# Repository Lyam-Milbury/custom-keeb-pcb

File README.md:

# 8/1 Macropad PCB
Repo for my (mis)adventures in creating a custom PCB for a macropad. I have always been a fan of custom keyboards. My daily driver is a stripped-down DROP ALT keyboard. I replaced the switches with ones that I hand-lubed, swapped the stabilizers with higher quality ones, and fitted custom keycaps to complete the build. After falling even further down the rabbit hole, the only natural progression of this hobby was clearly to create a custom PCB. This PCB has 8 slots for MX-hybrid switches (no LED pins) and 1 rotary encoder (hence, 8/1). The design of this build was inspired by ai03's <a href="https://wiki.ai03.com/books/pcb-design/chapter/pcb-designer-guide">PCB Designer Guide</a>.

## Software
KiCad 7.0 was used to create the schematics and design for the PCB. A custom footprint library, MX_ALPS_HYBRID, was used for the switch slot footprints, but everything else is available on vanilla KiCad.

## Schematics
The following are images of the schematics that were created in KiCad. This schematics file was then used to generate the PCB template.
### Microcontroller Unit

The Microcontroller unit (MCU) used for this project was the ATMega32U4-A. This microcontroller is perfect for this application, as this project did not require a large amount of processing power. It boasts a humble 44 pins, 24 of which can be used as bi-directional I/O ports for the signals sent by our key presses. This design could easily be scaled up to a fully sized keyboard matrix and this MCU would still have pins to spare. It also has 32 KBs of flash memory with is more than enough for the firmware that will be flashed onto it.

### Auxillary Units 

The rest of the schematics include the following:
* 3x4 keyboard matrix created using diodes as switches
* Decoupling capacitors to filter out electrical noise
* A crystal which controls the speed of the MCU
* A reset button for testing purposes
* The USB 2.0 circutry
  
|Keyboard Matrix|Decoupling Capacitor, Crystal, Reset Button, USB connection|
-----------------------|-------------------------------------------------------------
 | 

## PCB Designs

### Version 1 

This was the first design I came up with. As soon as I finished it, I already knew I wasn't too proud of it. The traces were messy and the placement of some of the components wasn't optimal.

### Version 2

Version two is the latest design. I moved the MCU and the reset switch to allow connections to be traced with more ease. IMore care in laying out the traces, opting for bus-style traces wherever I could. while keeping in mind that some traces needed to be intentionally isolated to prevent crosstalk. I knew this design would be good enough for production, so I also added final touches, such as the drill holes in the bottom corners, the ground fill in the top third to protect sensitive components from electrical noise, and a print of a little dude pressing the reset button.

## TODOs & Note
The design has already been sent to a manufacturer and is in production as I'm typing this. Once I receive the boards, if everything works as expected, here are the next steps I'll be taking to complete this project:
1. Solder components to the PCB
2. Use QMK to write custom macros
3. Design & 3d print enclosure

Designing this PCB has been a blast. I'm a computer engineer by education but I took more of a software-oriented route for my trade. This has reminded me of how much fun hardware design can be and will not be the last one design.

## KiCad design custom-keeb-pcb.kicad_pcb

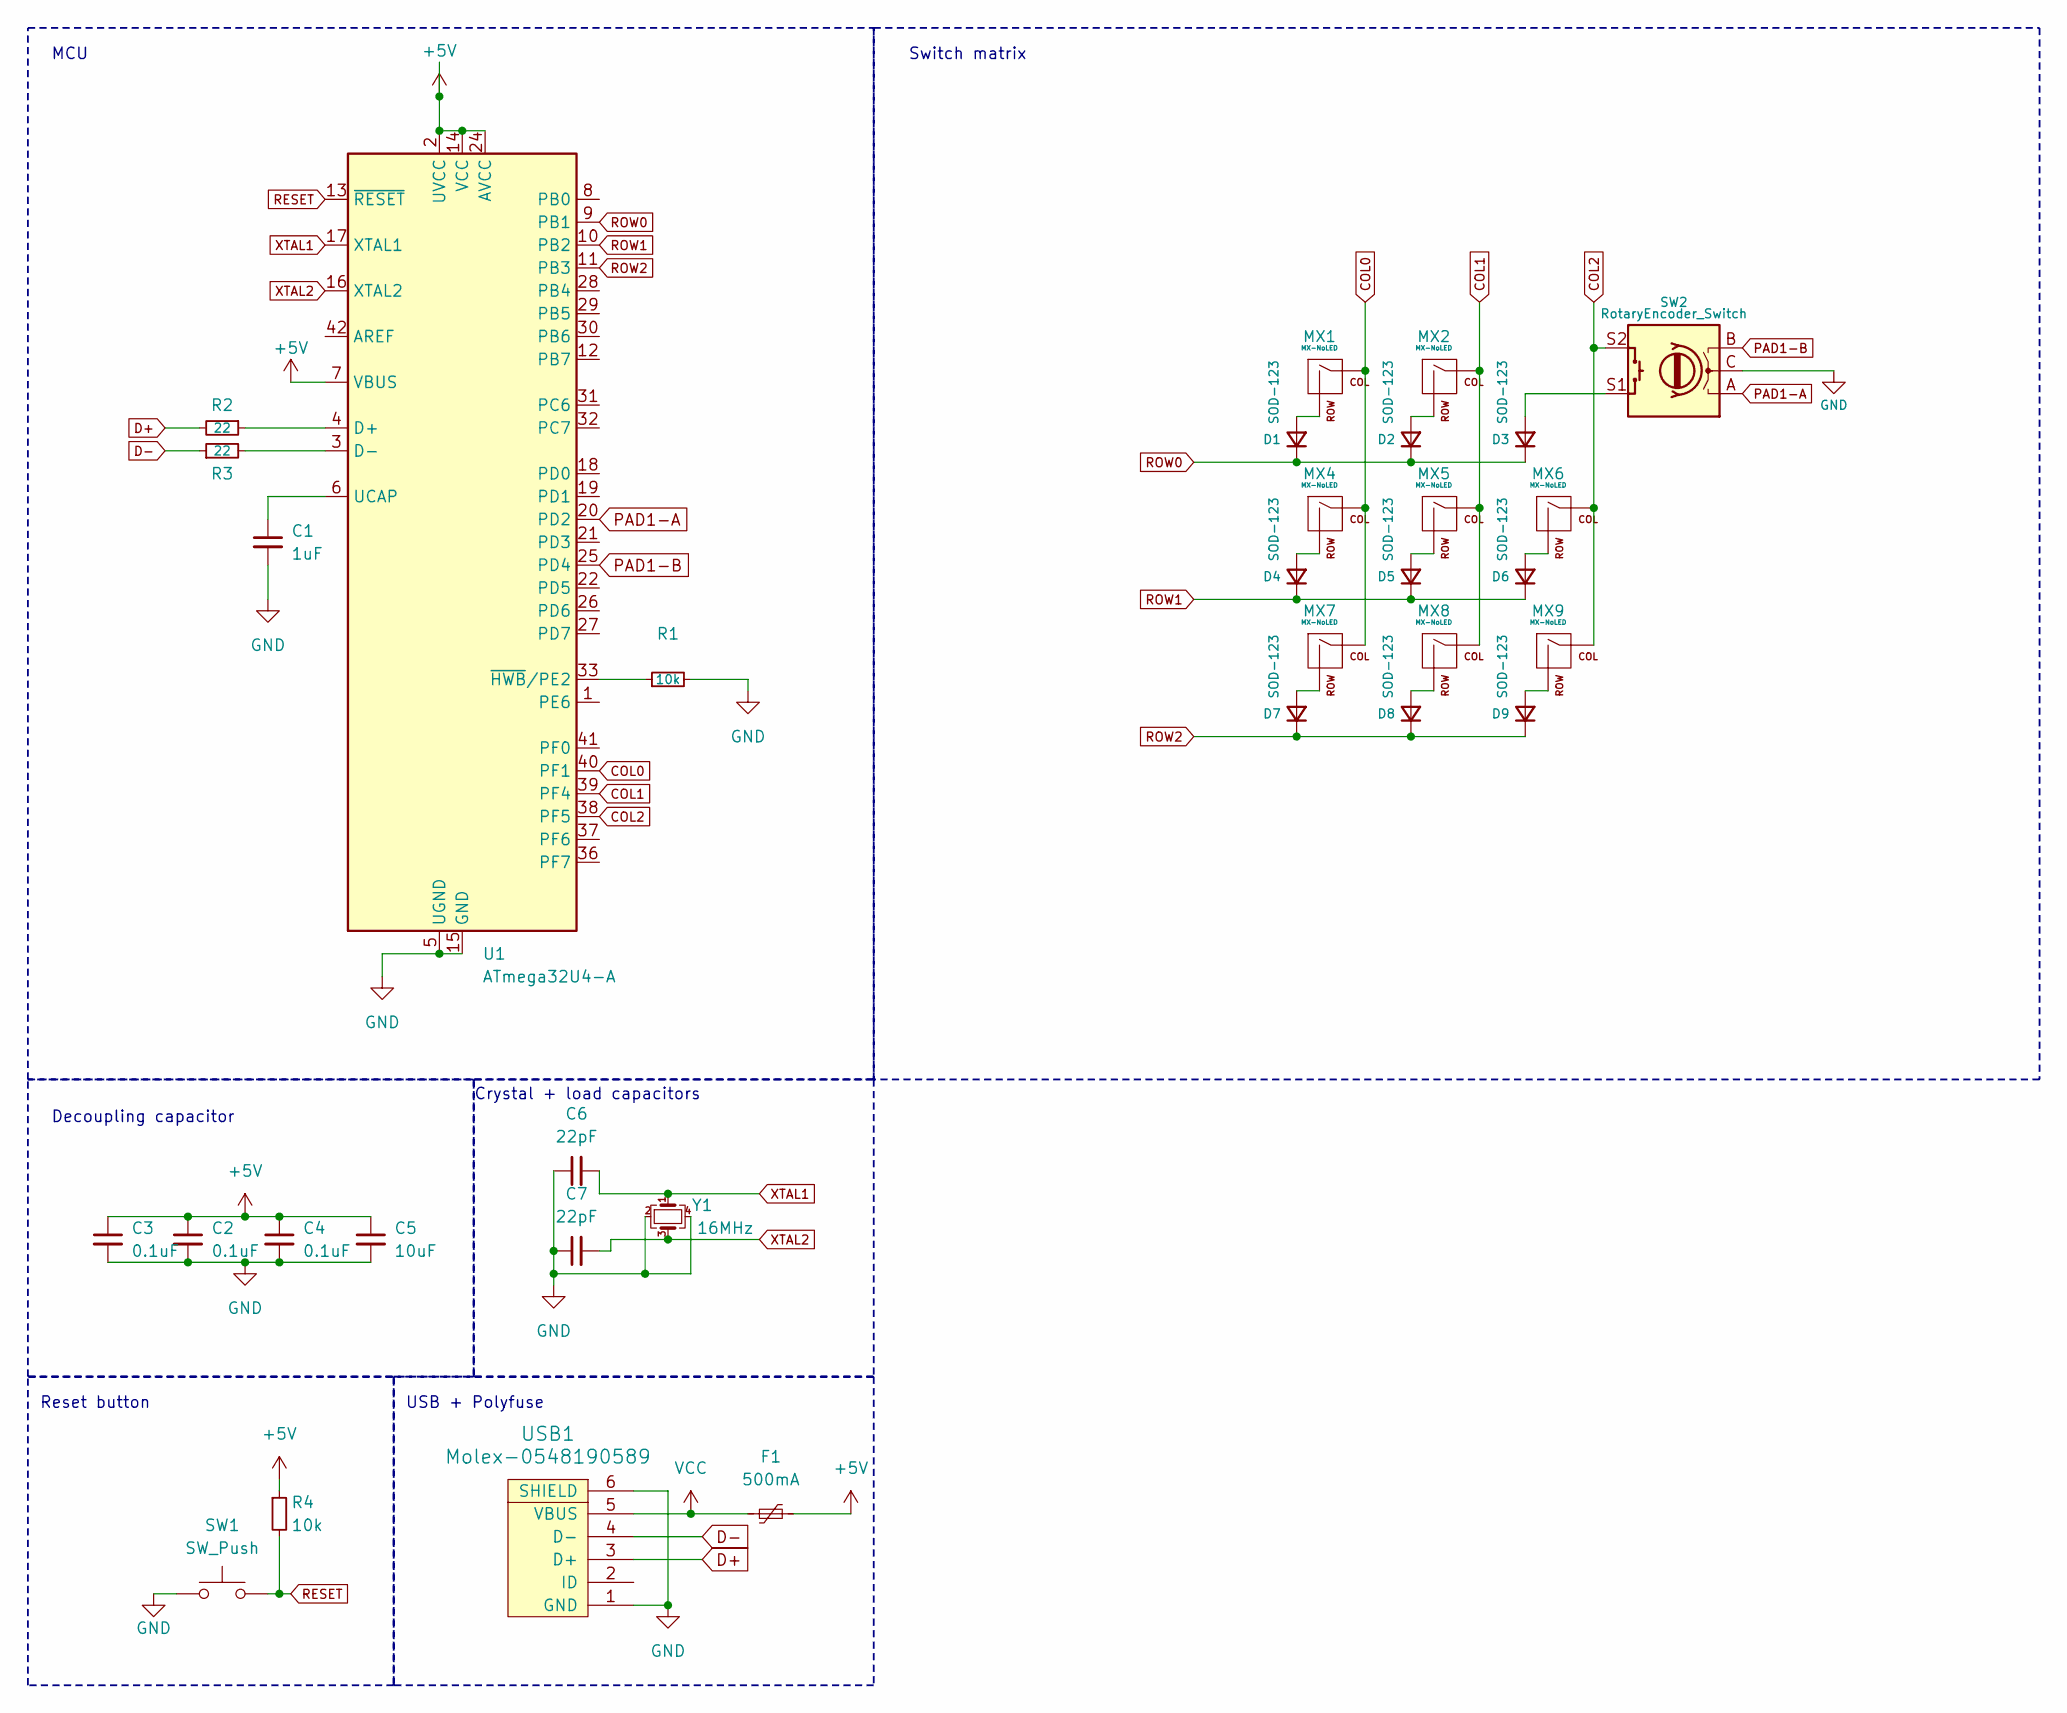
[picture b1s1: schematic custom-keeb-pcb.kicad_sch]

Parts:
C1: 1uF; C_0805_2012Metric
C2, C3, C4: 0.1uF; C_0805_2012Metric
C5: 10uF; C_0805_2012Metric
C6, C7: 22pF; C_0805_2012Metric
D1, D2, D3, D4, D5, D6, D7, D8, D9: SOD-123; D_SOD-123
F1: 500mA; Fuse_1206_3216Metric
MX1, MX2, MX4, MX5, MX6, MX7, MX8, MX9: MX-NoLED; MX-1U-NoLED
R1, R4: 10k; R_0805_2012Metric
R2, R3: 22; R_0805_2012Metric
SW1: SW_Push; SKQG-1155865
SW2: RotaryEncoder_Switch; RotaryEncoder_Alps_EC11E-Switch_Vertical_H20mm
U1: ATmega32U4-A; TQFP-44_10x10mm_P0.8mm
USB1: Molex-0548190589
Y1: 16MHz; Crystal_SMD_3225-4Pin_3.2x2.5mm

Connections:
+5V: C2.1, C3.1, C4.1, C5.1, F1.2, R4.1, U1.2 (UVCC), U1.7 (VBUS), U1.14 (VCC), U1.24 (AVCC), U1.34 (VCC), U1.44 (AVCC)
COL0: MX1.1 (COL), MX4.1 (COL), MX7.1 (COL), U1.40 (PF1)
COL1: MX2.1 (COL), MX5.1 (COL), MX8.1 (COL), U1.39 (PF4)
COL2: MX6.1 (COL), MX9.1 (COL), SW2.S2, U1.38 (PF5)
D+: R2.2, USB1.3 (D+)
D-: R3.1, USB1.4 (D-)
GND: C1.2, C2.2, C3.2, C4.2, C5.2, C6.1, C7.1, R1.2, SW1.1, SW2.C, U1.5 (UGND), U1.15 (GND), U1.23 (GND), U1.35 (GND), U1.43 (GND), USB1.1 (GND), USB1.6 (SHIELD), Y1.2, Y1.4
unnamed: D1.2 (A), MX1.2 (ROW)
unnamed: D2.2 (A), MX2.2 (ROW)
unnamed: D3.2 (A), SW2.S1
unnamed: D4.2 (A), MX4.2 (ROW)
unnamed: D5.2 (A), MX5.2 (ROW)
unnamed: D6.2 (A), MX6.2 (ROW)
unnamed: D7.2 (A), MX7.2 (ROW)
unnamed: D8.2 (A), MX8.2 (ROW)
unnamed: D9.2 (A), MX9.2 (ROW)
unnamed: R2.1, U1.4 (D+)
unnamed: R3.2, U1.3 (D-)
unnamed: C1.1, U1.6 (UCAP)
unnamed: R1.1, U1.33 (~HWB/PE2)
PAD1-A: SW2.A, U1.20 (PD2)
PAD1-B: SW2.B, U1.25 (PD4)
RESET: R4.2, SW1.2, U1.13 (~RESET)
ROW0: D1.1 (K), D2.1 (K), D3.1 (K), U1.9 (PB1)
ROW1: D4.1 (K), D5.1 (K), D6.1 (K), U1.10 (PB2)
ROW2: D7.1 (K), D8.1 (K), D9.1 (K), U1.11 (PB3)
VCC: F1.1, USB1.5 (VBUS)
XTAL1: C6.2, U1.17 (XTAL1), Y1.1
XTAL2: C7.2, U1.16 (XTAL2), Y1.3

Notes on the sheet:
Switch matrix
Reset button
Crystal + load capacitors
MCU
USB + Polyfuse
Decoupling capacitor

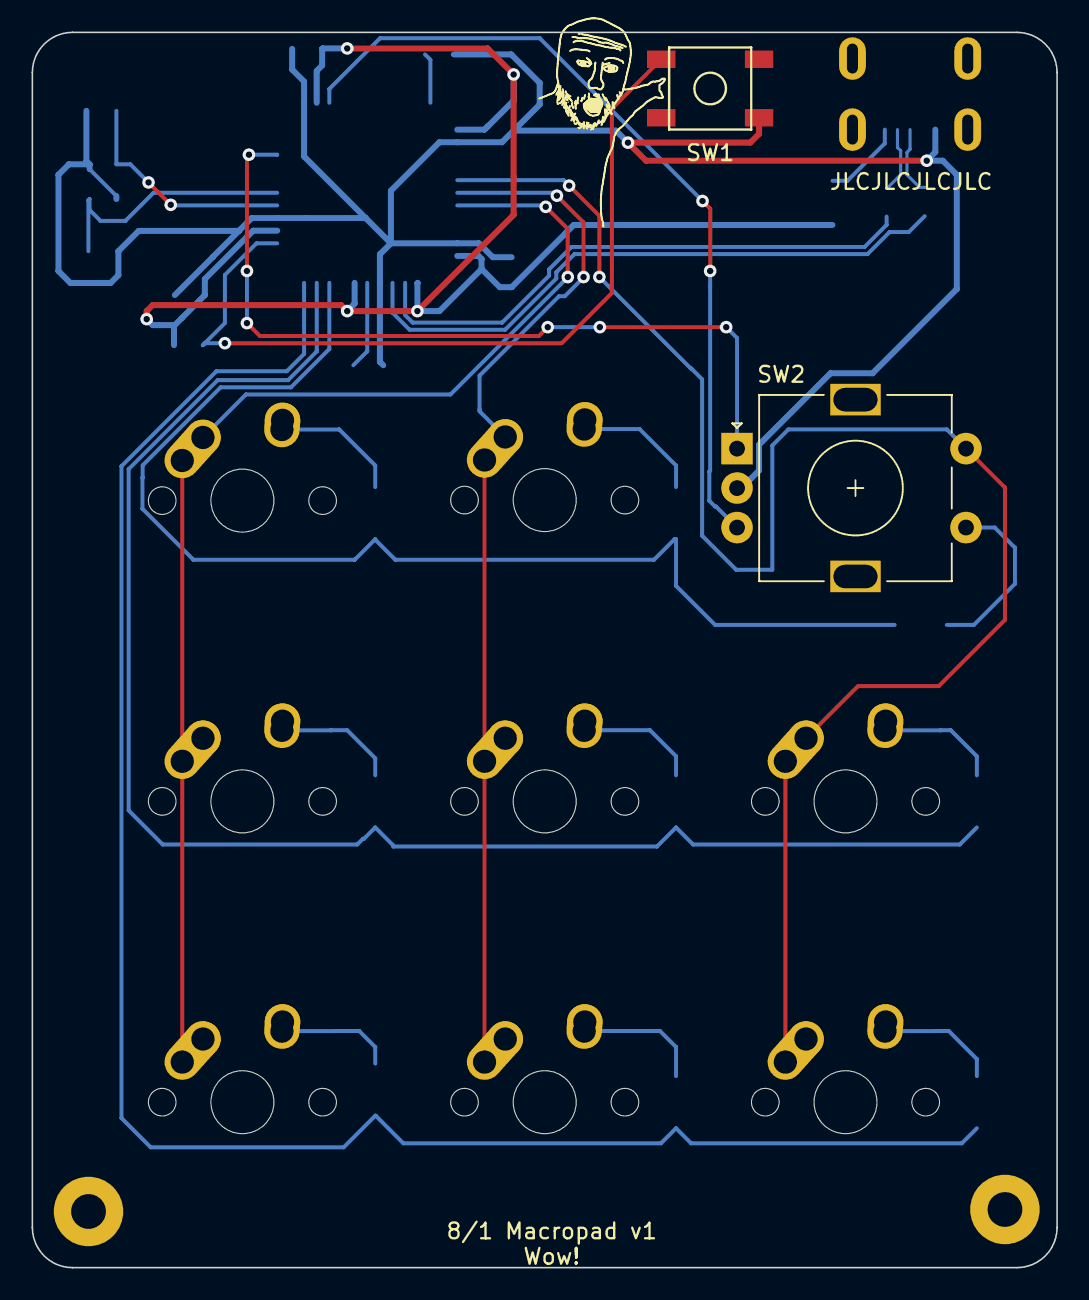
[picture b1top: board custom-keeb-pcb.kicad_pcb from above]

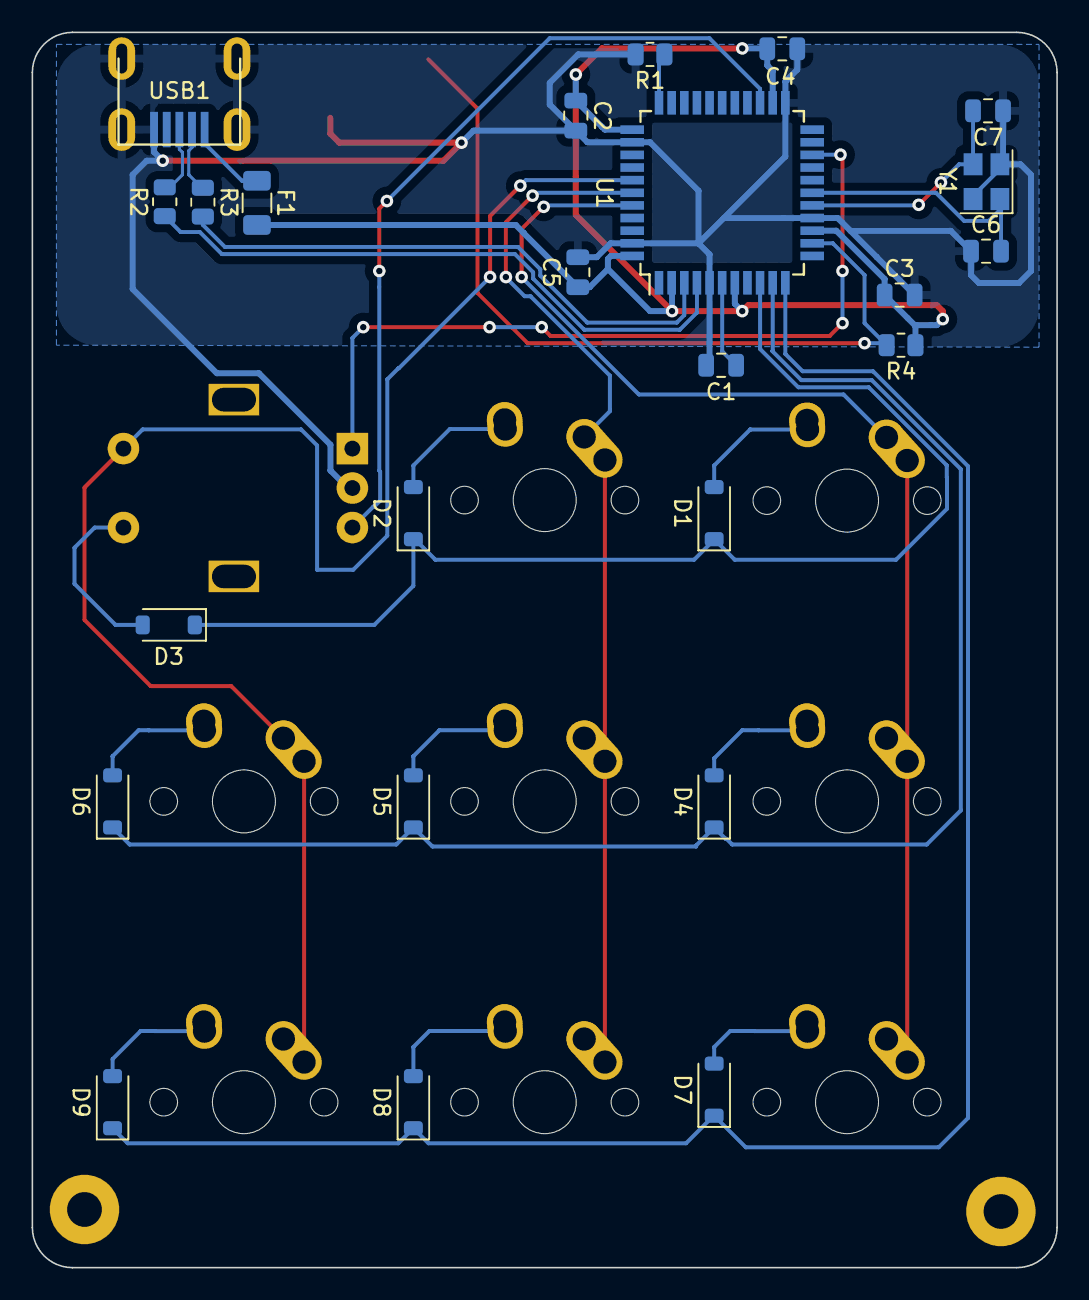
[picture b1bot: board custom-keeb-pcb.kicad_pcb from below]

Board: 2 copper layers, 64.9 x 78.2 mm, 35 parts (24 on the bottom side), 29 nets.

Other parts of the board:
G1: LOGO; pcbjack

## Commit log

2024-01-29 Init commit
2024-01-30 Added submodules
2024-01-30 Added footprint libraries
2024-01-30 KiCad schematic of PCB
2024-01-31 Completed v1 of PCB design
2024-02-02 Finished v2 Design
    Rerouted traces, added fill, added decals & text. Ready for printing
2024-02-13 Update README.md
    Removed some flavor text
